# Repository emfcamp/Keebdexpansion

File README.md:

# KeebDeck Hexpansion

A keyboard hexpansion for the [Tildagon badge](https://tildagon.badge.emfcamp.org/) using the [solder.party KeebDeck Keyboard](https://www.solder.party/docs/keebdeck/keyboard/). Software for the hexpansion is [provided by @sodoku](https://github.com/sodoku/tildagon-keebdeck).

## Features

- Full layout keyboard
- RGB Backlit keys
- Type in text inputs
- Auto-installs driver when plugged in

Available for EMF 2026 camp ticket holders on the emfcamp website. See [here](https://blog.emfcamp.org/2026/05/28/tildagon-2026-spaceagon/) for more info

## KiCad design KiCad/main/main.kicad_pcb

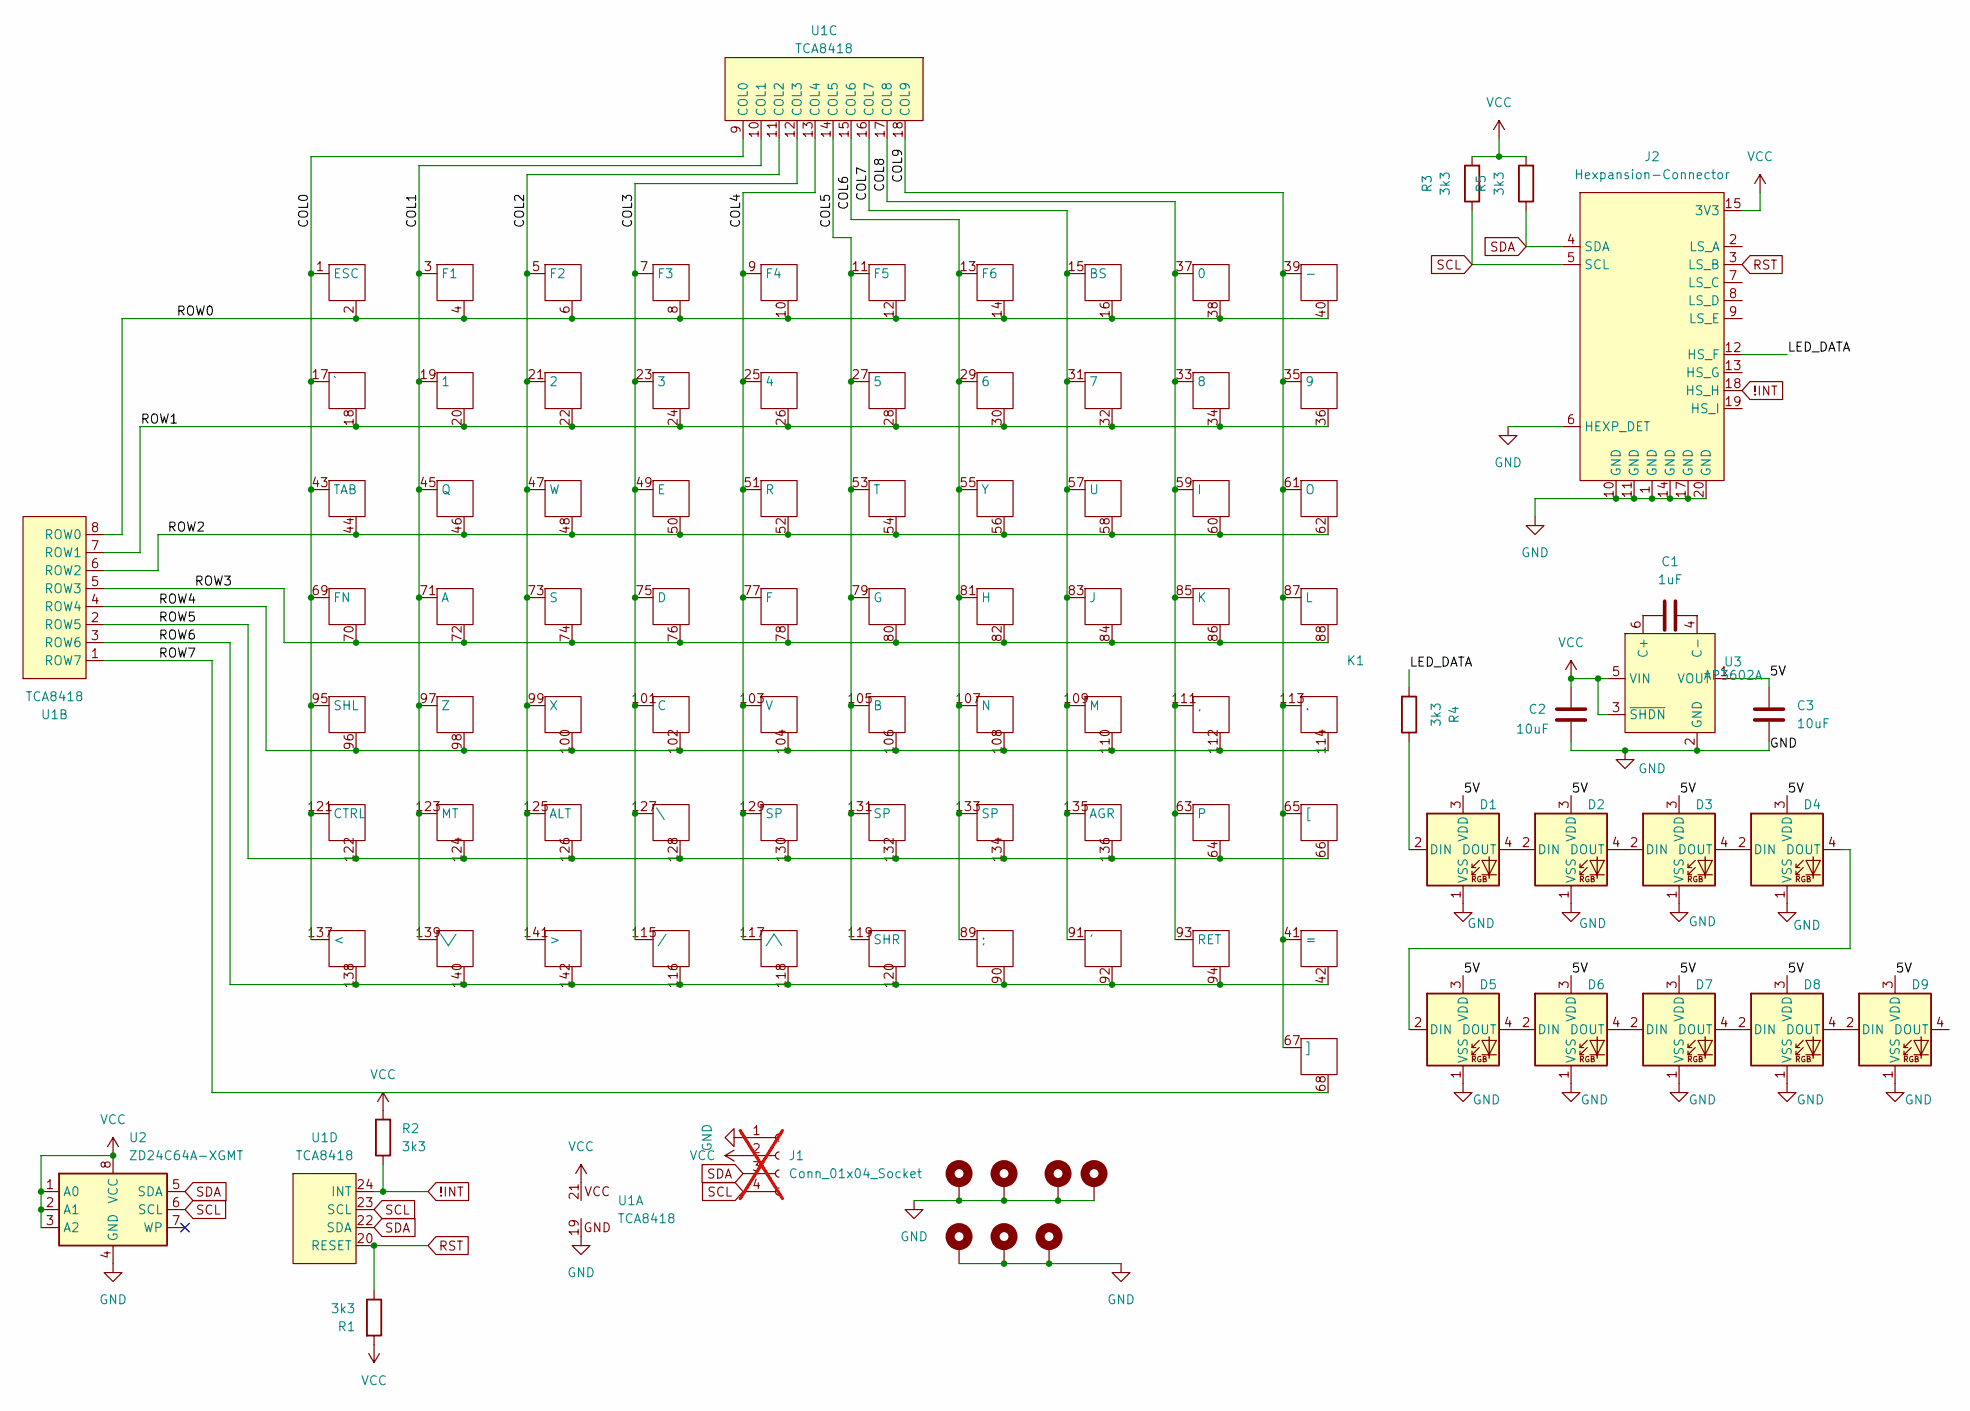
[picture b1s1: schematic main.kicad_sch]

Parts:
C1: 1uF; C_0402_1005Metric; MPN C2887021
C2, C3: 10uF; C_0603_1608Metric; MPN C3015157
D1, D2, D3, D4, D5, D6, D7, D8, D9: XL-3210RGBC-WS2812B; XL-3210RGBC-2812B; MPN C41413182
H1, H3: MountingHole_Pad; MountingHole_2.2mm_M2_Pad_Via
H2, H4, H5, H6, H7: SMTSO2020CTJ; LCSC C2915626
J1: Conn_01x04_Socket; JST_SH_SM04B-SRSS-TB_1x04-1MP_P1.00mm_Horizontal; not fitted
J2: Hexpansion-Connector; hexpansion-edge-connector
K1: keyboard_arturo182
R1, R2, R3, R4, R5: 3k3; R_0603_1608Metric_Pad0.98x0.95mm_HandSolder
U1: TCA8418; WQFN-24-1EP_4x4mm_P0.5mm_EP2.45x2.45mm
U2: ZD24C64A-XGMT; TSSOP-8_4.4x3mm_P0.65mm; MPN C2875852
U3: AP3602A; TSOT-23-6_HandSoldering; MPN C460358

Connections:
!INT: J2.18 (HS_H), R2.1, U1.24 (INT)
/5V: C3.2, D1.3 (VDD), D2.3 (VDD), D3.3 (VDD), D4.3 (VDD), D5.3 (VDD), D6.3 (VDD), D7.3 (VDD), D8.3 (VDD), D9.3 (VDD), U3.1 (VOUT)
/COL0: K1.1 (ESC), K1.17 (`), K1.43 (TAB), K1.69 (FN), K1.95 (SHL), K1.121 (CTRL), K1.137 (<), U1.9 (COL0)
/COL1: K1.3 (F1), K1.19 (1), K1.45 (Q), K1.71 (A), K1.97 (Z), K1.123 (MT), K1.139 (\/), U1.10 (COL1)
/COL2: K1.5 (F2), K1.21 (2), K1.47 (W), K1.73 (S), K1.99 (X), K1.125 (ALT), K1.141 (>), U1.11 (COL2)
/COL3: K1.7 (F3), K1.23 (3), K1.49 (E), K1.75 (D), K1.101 (C), K1.115 (/), K1.127 (\), U1.12 (COL3)
/COL4: K1.9 (F4), K1.25 (4), K1.51 (R), K1.77 (F), K1.103 (V), K1.117 (/\), K1.129 (SP), U1.13 (COL4)
/COL5: K1.11 (F5), K1.27 (5), K1.53 (T), K1.79 (G), K1.105 (B), K1.119 (SHR), K1.131 (SP), U1.14 (COL5)
/COL6: K1.13 (F6), K1.29 (6), K1.55 (Y), K1.81 (H), K1.89 (;), K1.107 (N), K1.133 (SP), U1.15 (COL6)
/COL7: K1.15 (BS), K1.31 (7), K1.57 (U), K1.83 (J), K1.91 ('), K1.109 (M), K1.135 (AGR), U1.16 (COL7)
/COL8: K1.33 (8), K1.37 (0), K1.59 (I), K1.63, K1.85 (K), K1.93 (RET), K1.111 (,), U1.17 (COL8)
/COL9: K1.35 (9), K1.39 (-), K1.41 (=), K1.61 (O), K1.65 ([), K1.67 (]), K1.87 (L), K1.113 (.), U1.18 (COL9)
/LED_DATA: J2.12 (HS_F), R4.2
/ROW0: K1.2, K1.4, K1.6, K1.8, K1.10, K1.12, K1.14, K1.16, K1.38, K1.40, U1.8 (ROW0)
/ROW1: K1.18, K1.20, K1.22, K1.24, K1.26, K1.28, K1.30, K1.32, K1.34, K1.36, U1.7 (ROW1)
/ROW2: K1.44, K1.46, K1.48, K1.50, K1.52, K1.54, K1.56, K1.58, K1.60, K1.62, U1.6 (ROW2)
/ROW3: K1.70, K1.72, K1.74, K1.76, K1.78, K1.80, K1.82, K1.84, K1.86, K1.88, U1.5 (ROW3)
/ROW4: K1.96, K1.98, K1.100, K1.102, K1.104, K1.106, K1.108, K1.110, K1.112, K1.114, U1.4 (ROW4)
/ROW5: K1.64, K1.66, K1.122, K1.124, K1.126, K1.128, K1.130, K1.132, K1.134, K1.136, U1.2 (ROW5)
/ROW6: K1.42, K1.90, K1.92, K1.94, K1.116, K1.118, K1.120, K1.138, K1.140, K1.142, U1.3 (ROW6)
/ROW7: K1.68, U1.1 (ROW7)
GND: C2.1, C3.1, D1.1 (VSS), D2.1 (VSS), D3.1 (VSS), D4.1 (VSS), D5.1 (VSS), D6.1 (VSS), D7.1 (VSS), D8.1 (VSS), D9.1 (VSS), H1.1, H2.1, H3.1, H4.1, H5.1, H6.1, H7.1, J1.1, J2.1 (GND), J2.6 (HEXP_DET), J2.10 (GND), J2.11 (GND), J2.14 (GND), J2.17 (GND), J2.20 (GND), U1.19, U2.4 (GND), U3.2 (GND)
unnamed: D1.2 (DIN), R4.1
unnamed: D1.4 (DOUT), D2.2 (DIN)
unnamed: D2.4 (DOUT), D3.2 (DIN)
unnamed: D3.4 (DOUT), D4.2 (DIN)
unnamed: D4.4 (DOUT), D5.2 (DIN)
unnamed: D5.4 (DOUT), D6.2 (DIN)
unnamed: D6.4 (DOUT), D7.2 (DIN)
unnamed: D7.4 (DOUT), D8.2 (DIN)
unnamed: D8.4 (DOUT), D9.2 (DIN)
unnamed: C1.1, U3.6 (C+)
unnamed: C1.2, U3.4 (C-)
RST: J2.3 (LS_B), R1.1, U1.20 (RESET)
SCL: J1.4, J2.5 (SCL), R3.1, U1.23 (SCL), U2.6 (SCL)
SDA: J1.3, J2.4 (SDA), R5.1, U1.22 (SDA), U2.5 (SDA)
VCC: C2.2, J1.2, J2.15 (3V3), J2.16 (3V3), R1.2, R2.2, R3.2, R5.2, U1.21, U2.1 (A0), U2.2 (A1), U2.3 (A2), U2.8 (VCC), U3.3 (~SHDN), U3.5 (VIN)

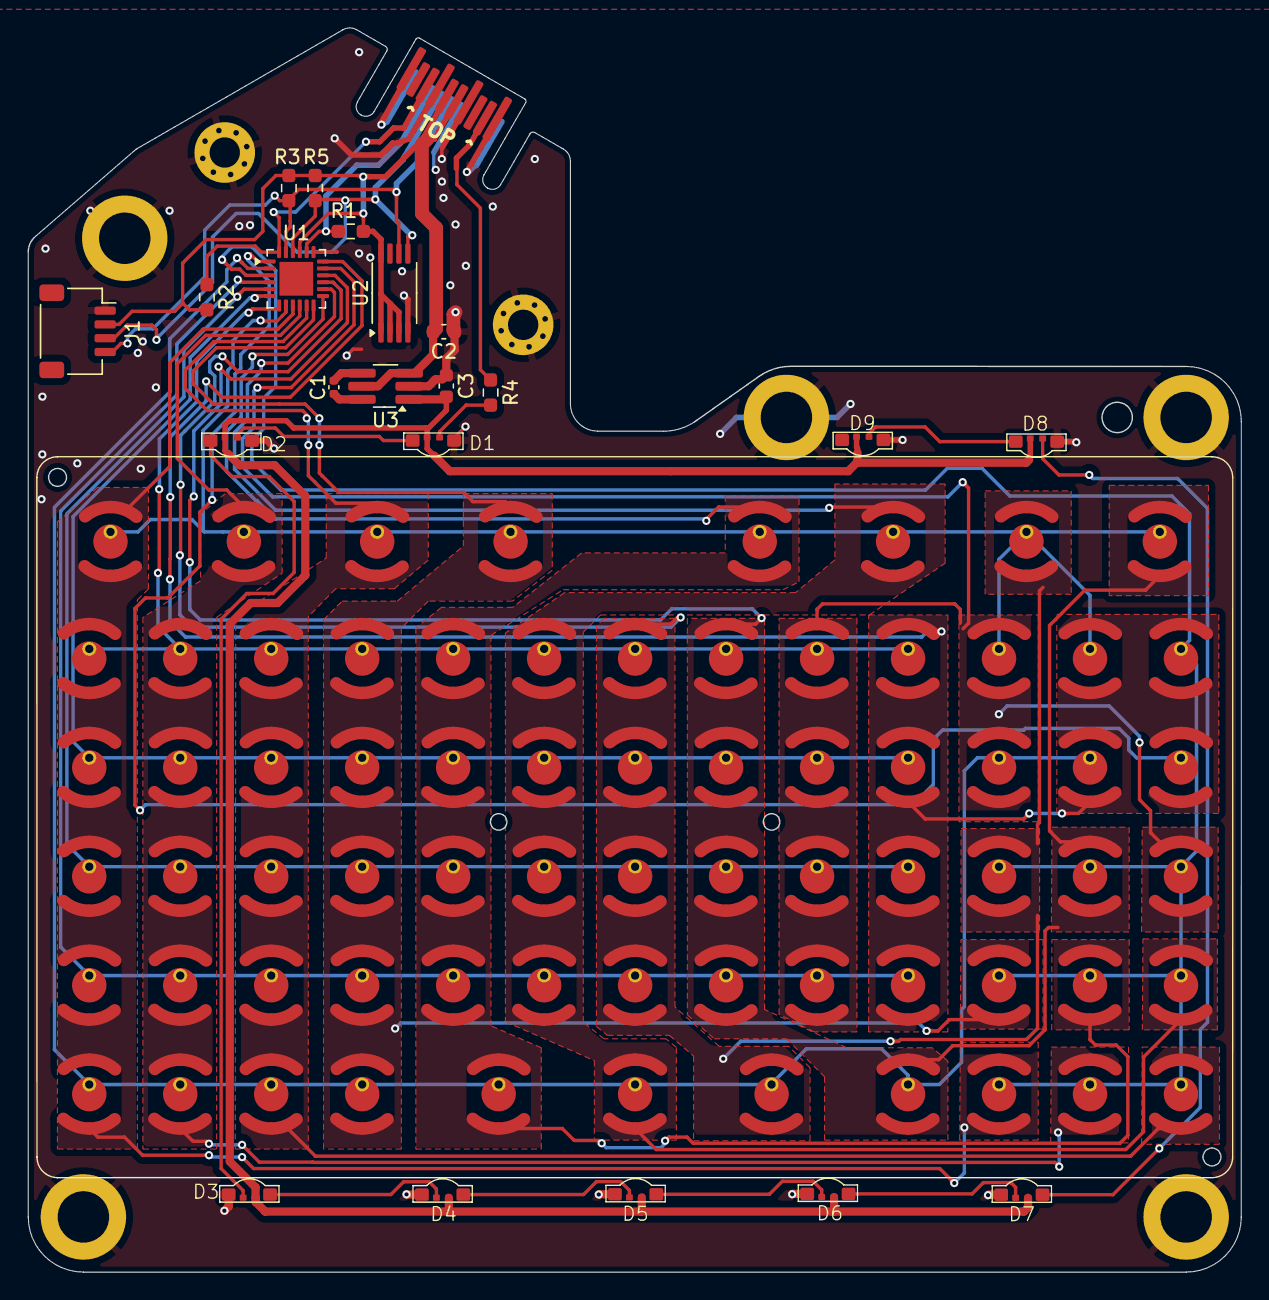
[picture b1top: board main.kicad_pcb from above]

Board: 2 copper layers, 88.0 x 90.2 mm, 30 parts (0 on the bottom side), 37 nets.

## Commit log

2026-06-11 Modify for EMF camp - Change shape - Move standoffs to bottom PCB - Add RGB LEDs and power conversion for them - Add art - Generate and add 3D models
2026-06-11 Update docs
2026-06-11 Convert board cutouts to polygons to work around a STEP export bug
